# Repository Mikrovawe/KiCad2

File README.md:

# Input Output device

School assignment

In this assignment I received the schematic for this input/output device.
My task was to design the functional blocks and create the documentation as well as designing the 4-layer pcb using KiCad.

In file XX there is the planning of the design

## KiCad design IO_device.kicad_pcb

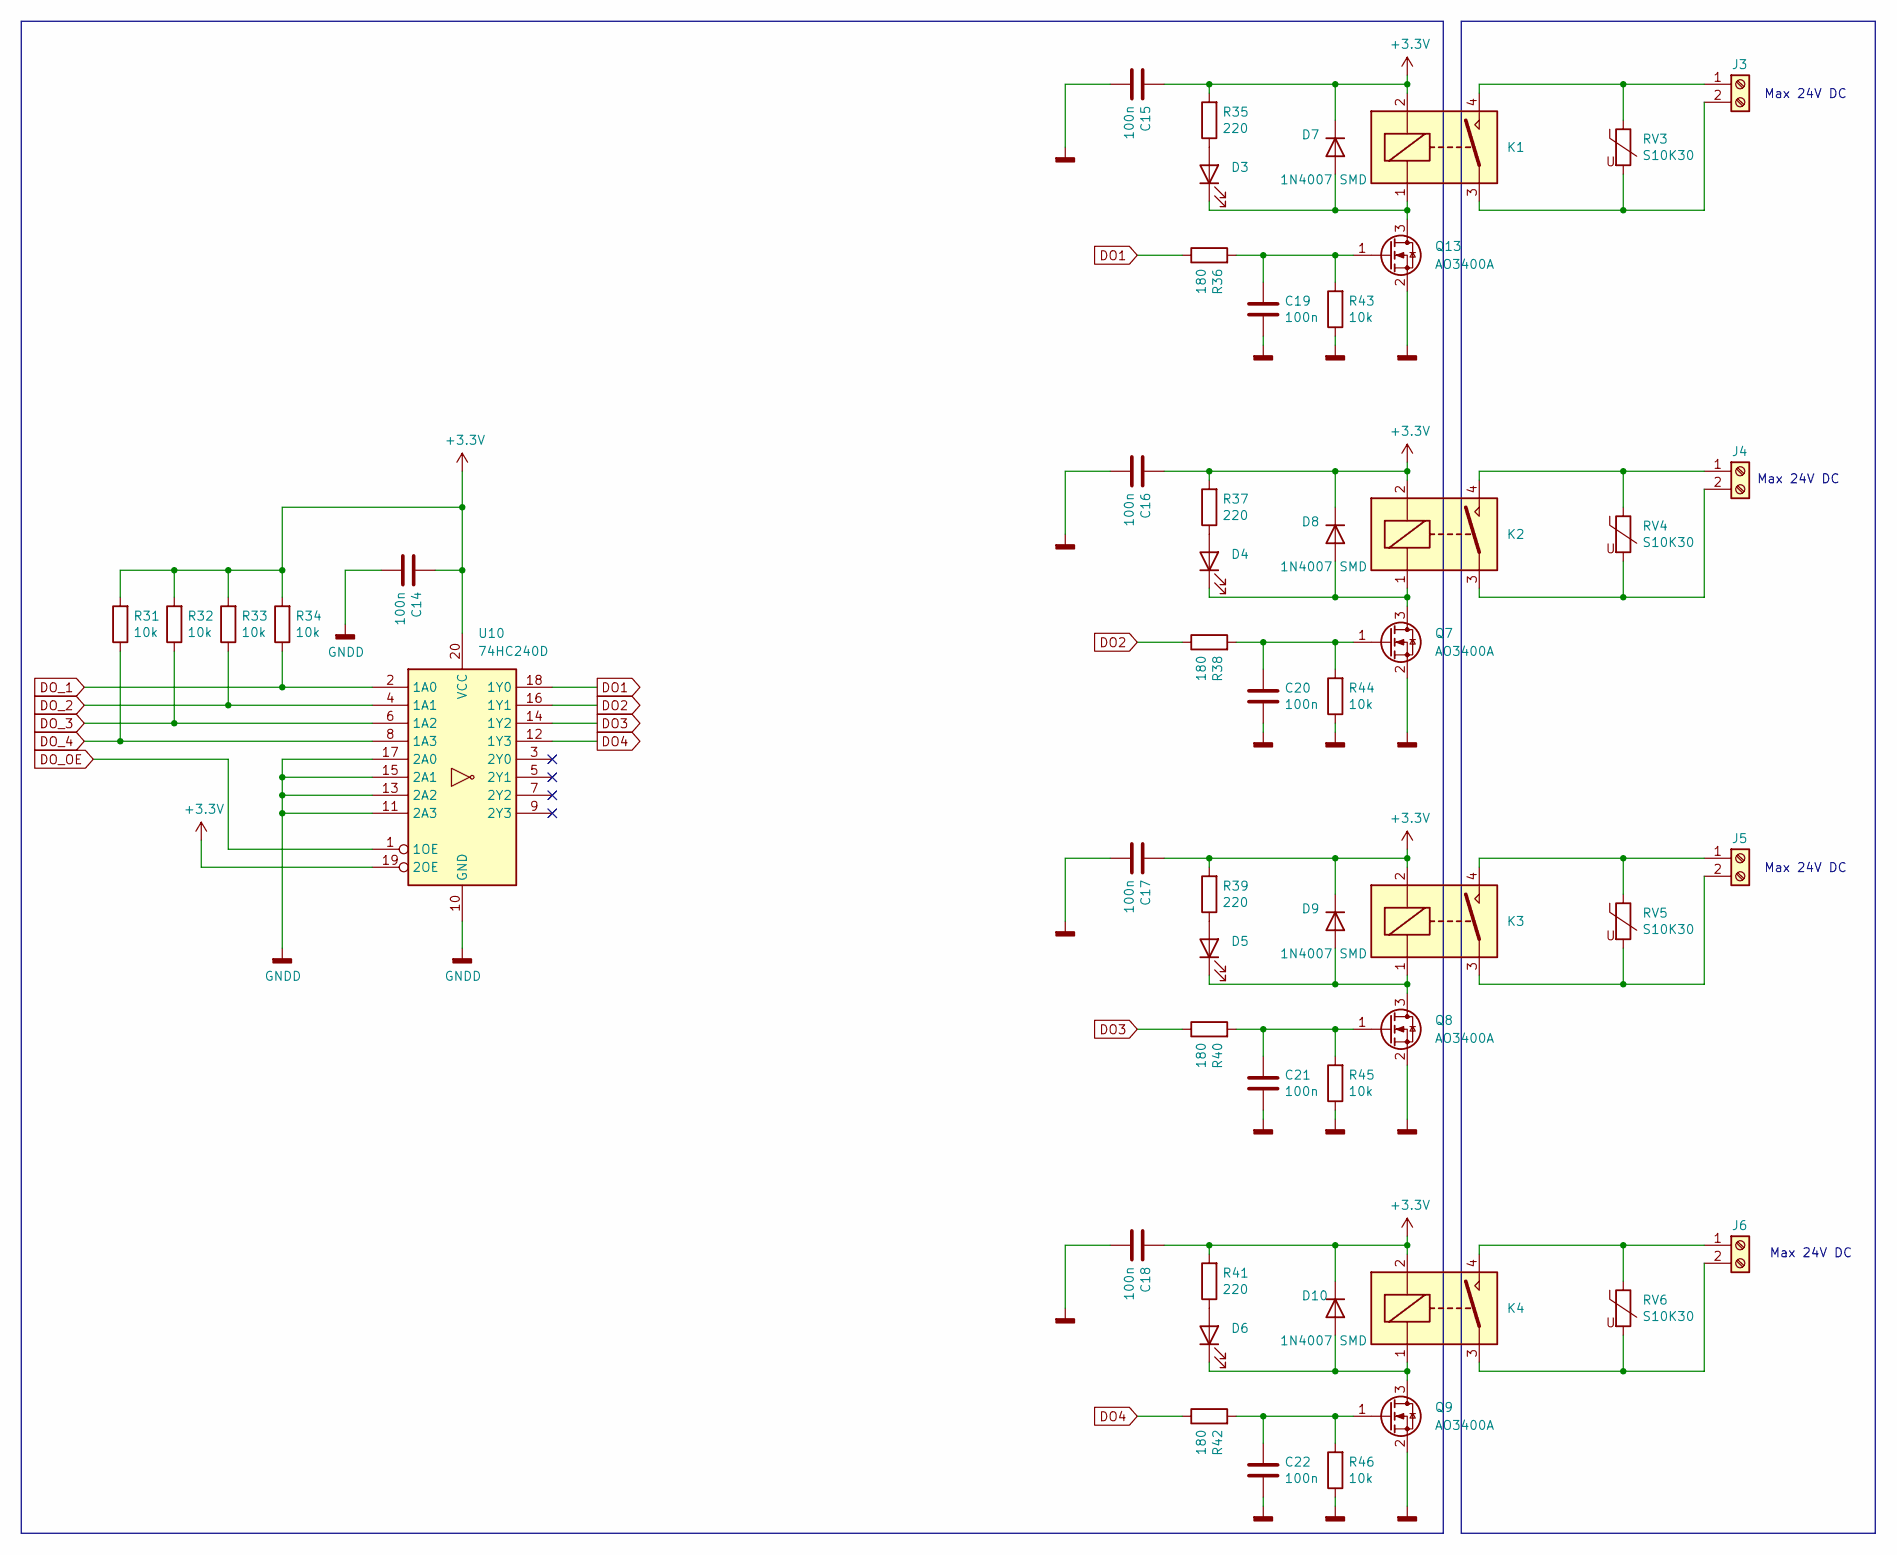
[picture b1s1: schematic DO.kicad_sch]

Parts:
C14, C15, C16, C17, C18, C19, C20, C21, C22: 100n; C_1206_3216Metric
D3, D4, D5, D6: Green LED 3mm; D_1206_3216Metric
D7, D8, D9, D10: 1N4007 SMD; D_SOD-123
J3, J4, J5, J6: Screw_Terminal_01x02; TerminalBlock_Phoenix_MKDS-3-2-5.08_1x02_P5.08mm_Horizontal
K1, K2, K3, K4: SDT-S-103DMR,000; 1461267-1
Q7, Q8, Q9, Q13: AO3400A; SOT-23
R31, R32, R33, R34, R43, R44, R45, R46: 10k; R_1206_3216Metric
R35, R37, R39, R41: 220; R_1206_3216Metric
R36, R38, R40, R42: 180; R_1206_3216Metric
RV3, RV4, RV5, RV6: S10K30; RV_Disc_D12mm_W5.1mm_P7.5mm
U10: 74HC240D; SOIC-20W_7.5x12.8mm_P1.27mm

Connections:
+3.3V: C14.1, C15.1, C16.1, C17.1, C18.1, D7.1 (K), D8.1 (K), D9.1 (K), D10.1 (K), K1.2, K2.2, K3.2, K4.2, R31.2, R32.2, R33.2, R34.2, R35.2, R37.2, R39.2, R41.2, U10.19 (2OE), U10.20 (VCC); also elsewhere on the board
DO1: R36.1, U10.18 (1Y0)
DO2: R38.1, U10.16 (1Y1)
DO3: R40.1, U10.14 (1Y2)
DO4: R42.1, U10.12 (1Y3)
DO_1: R34.1, U10.2 (1A0); also elsewhere on the board
DO_2: R33.1, U10.4 (1A1); also elsewhere on the board
DO_3: R32.1, U10.6 (1A2); also elsewhere on the board
DO_4: R31.1, U10.8 (1A3); also elsewhere on the board
DO_OE: U10.1 (1OE); also elsewhere on the board
GNDD: C14.2, C15.2, C16.2, C17.2, C18.2, C19.2, C20.2, C21.2, C22.2, Q7.2 (S), Q8.2 (S), Q9.2 (S), Q13.2 (S), R43.1, R44.1, R45.1, R46.1, U10.10 (GND), U10.11 (2A3), U10.13 (2A2), U10.15 (2A1), U10.17 (2A0); also elsewhere on the board
unnamed: D3.2 (A), R35.1
unnamed: D3.1 (K), D7.2 (A), K1.1, Q13.3 (D)
unnamed: D4.2 (A), R37.1
unnamed: D4.1 (K), D8.2 (A), K2.1, Q7.3 (D)
unnamed: D5.2 (A), R39.1
unnamed: D5.1 (K), D9.2 (A), K3.1, Q8.3 (D)
unnamed: D6.2 (A), R41.1
unnamed: D6.1 (K), D10.2 (A), K4.1, Q9.3 (D)
unnamed: J3.1, K1.4, RV3.1
unnamed: J3.2, K1.3, RV3.2
unnamed: J4.1, K2.4, RV4.1
unnamed: J4.2, K2.3, RV4.2
unnamed: J5.1, K3.4, RV5.1
unnamed: J5.2, K3.3, RV5.2
unnamed: J6.1, K4.4, RV6.1
unnamed: J6.2, K4.3, RV6.2
unnamed: C20.1, Q7.1 (G), R38.2, R44.2
unnamed: C21.1, Q8.1 (G), R40.2, R45.2
unnamed: C22.1, Q9.1 (G), R42.2, R46.2
unnamed: C19.1, Q13.1 (G), R36.2, R43.2

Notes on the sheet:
Max 24V DC

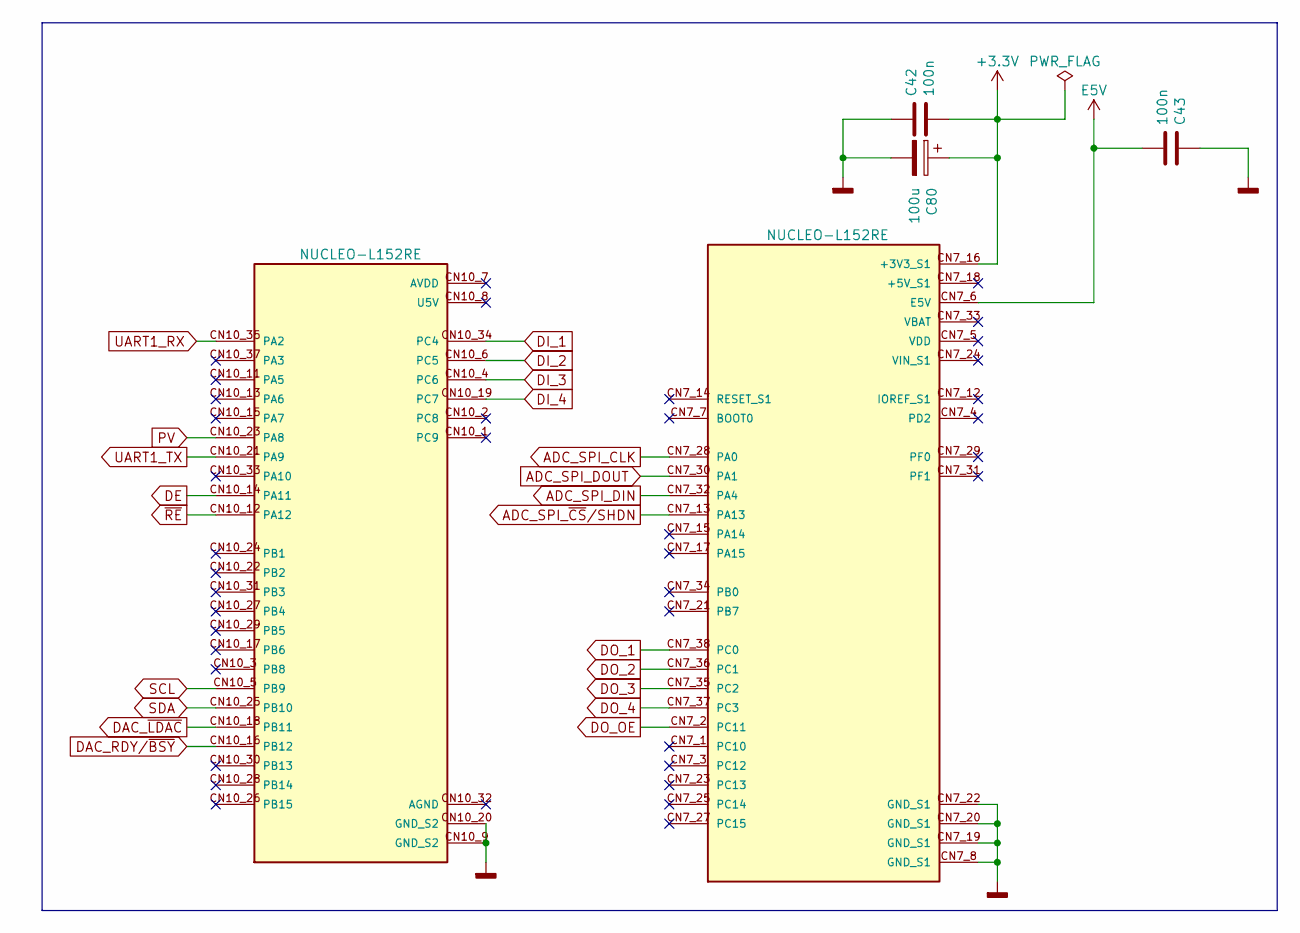
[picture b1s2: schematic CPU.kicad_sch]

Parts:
C42, C43: 100n; C_1206_3216Metric; Voltage 250V
C80: 100u; CP_Elec_6.3x7.7
U28: NUCLEO-L152RE; ST_NUCLEO-F303RE; PARTREV 14

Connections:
+3.3V: C42.2, C80.1, U28.CN7_16 (+3V3_S1); also elsewhere on the board
ADC_SPI_CLK: U28.CN7_28 (PA0); also elsewhere on the board
ADC_SPI_DIN: U28.CN7_32 (PA4); also elsewhere on the board
ADC_SPI_DOUT: U28.CN7_30 (PA1); also elsewhere on the board
ADC_SPI_~CS/SHDN: U28.CN7_13 (PA13); also elsewhere on the board
DAC_RDY/~BSY: U28.CN10_16 (PB12); also elsewhere on the board
DAC_~LDAC: U28.CN10_18 (PB11); also elsewhere on the board
DE: U28.CN10_14 (PA11); also elsewhere on the board
DI_1: U28.CN10_34 (PC4); also elsewhere on the board
DI_2: U28.CN10_6 (PC5); also elsewhere on the board
DI_3: U28.CN10_4 (PC6); also elsewhere on the board
DI_4: U28.CN10_19 (PC7); also elsewhere on the board
DO_1: U28.CN7_38 (PC0); also elsewhere on the board
DO_2: U28.CN7_36 (PC1); also elsewhere on the board
DO_3: U28.CN7_35 (PC2); also elsewhere on the board
DO_4: U28.CN7_37 (PC3); also elsewhere on the board
DO_OE: U28.CN7_2 (PC11); also elsewhere on the board
E5V: C43.2, U28.CN7_6 (E5V); also elsewhere on the board
GNDD: C42.1, C43.1, C80.2, U28.CN7_8 (GND_S1), U28.CN7_19 (GND_S1), U28.CN7_20 (GND_S1), U28.CN7_22 (GND_S1), U28.CN10_9 (GND_S2), U28.CN10_20 (GND_S2); also elsewhere on the board
PV: U28.CN10_23 (PA8); also elsewhere on the board
SCL: U28.CN10_5 (PB9); also elsewhere on the board
SDA: U28.CN10_25 (PB10); also elsewhere on the board
UART1_RX: U28.CN10_35 (PA2); also elsewhere on the board
UART1_TX: U28.CN10_21 (PA9); also elsewhere on the board
~RE: U28.CN10_12 (PA12); also elsewhere on the board

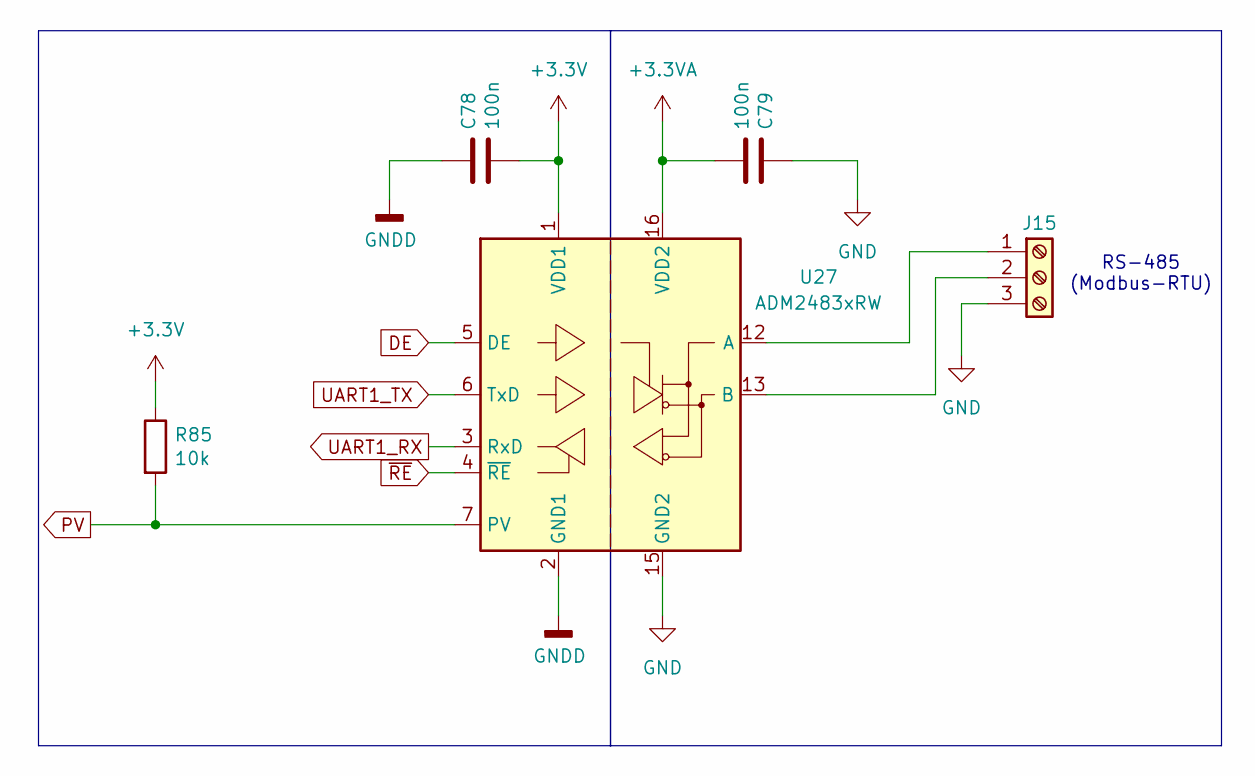
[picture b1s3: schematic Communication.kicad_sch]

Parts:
C78, C79: 100n; C_1206_3216Metric; Voltage 250V
J15: Screw_Terminal_01x03; TerminalBlock_Phoenix_MKDS-3-3-5.08_1x03_P5.08mm_Horizontal
R85: 10k; C_1206_3216Metric
U27: ADM2483xRW; SOIC-16W_7.5x10.3mm_P1.27mm

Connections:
+3.3V: C78.2, R85.1, U27.1 (VDD1); also elsewhere on the board
+3.3VA: C79.2, U27.16 (VDD2); also elsewhere on the board
DE: U27.5 (DE); also elsewhere on the board
GND: C79.1, J15.3, U27.9 (GND2), U27.15 (GND2); also elsewhere on the board
GNDD: C78.1, U27.2 (GND1), U27.8 (GND1); also elsewhere on the board
unnamed: J15.1, U27.12 (A)
unnamed: J15.2, U27.13 (B)
PV: R85.2, U27.7 (PV); also elsewhere on the board
UART1_RX: U27.3 (RxD); also elsewhere on the board
UART1_TX: U27.6 (TxD); also elsewhere on the board
~RE: U27.4 (~RE); also elsewhere on the board

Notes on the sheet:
RS-485 (Modbus-RTU)

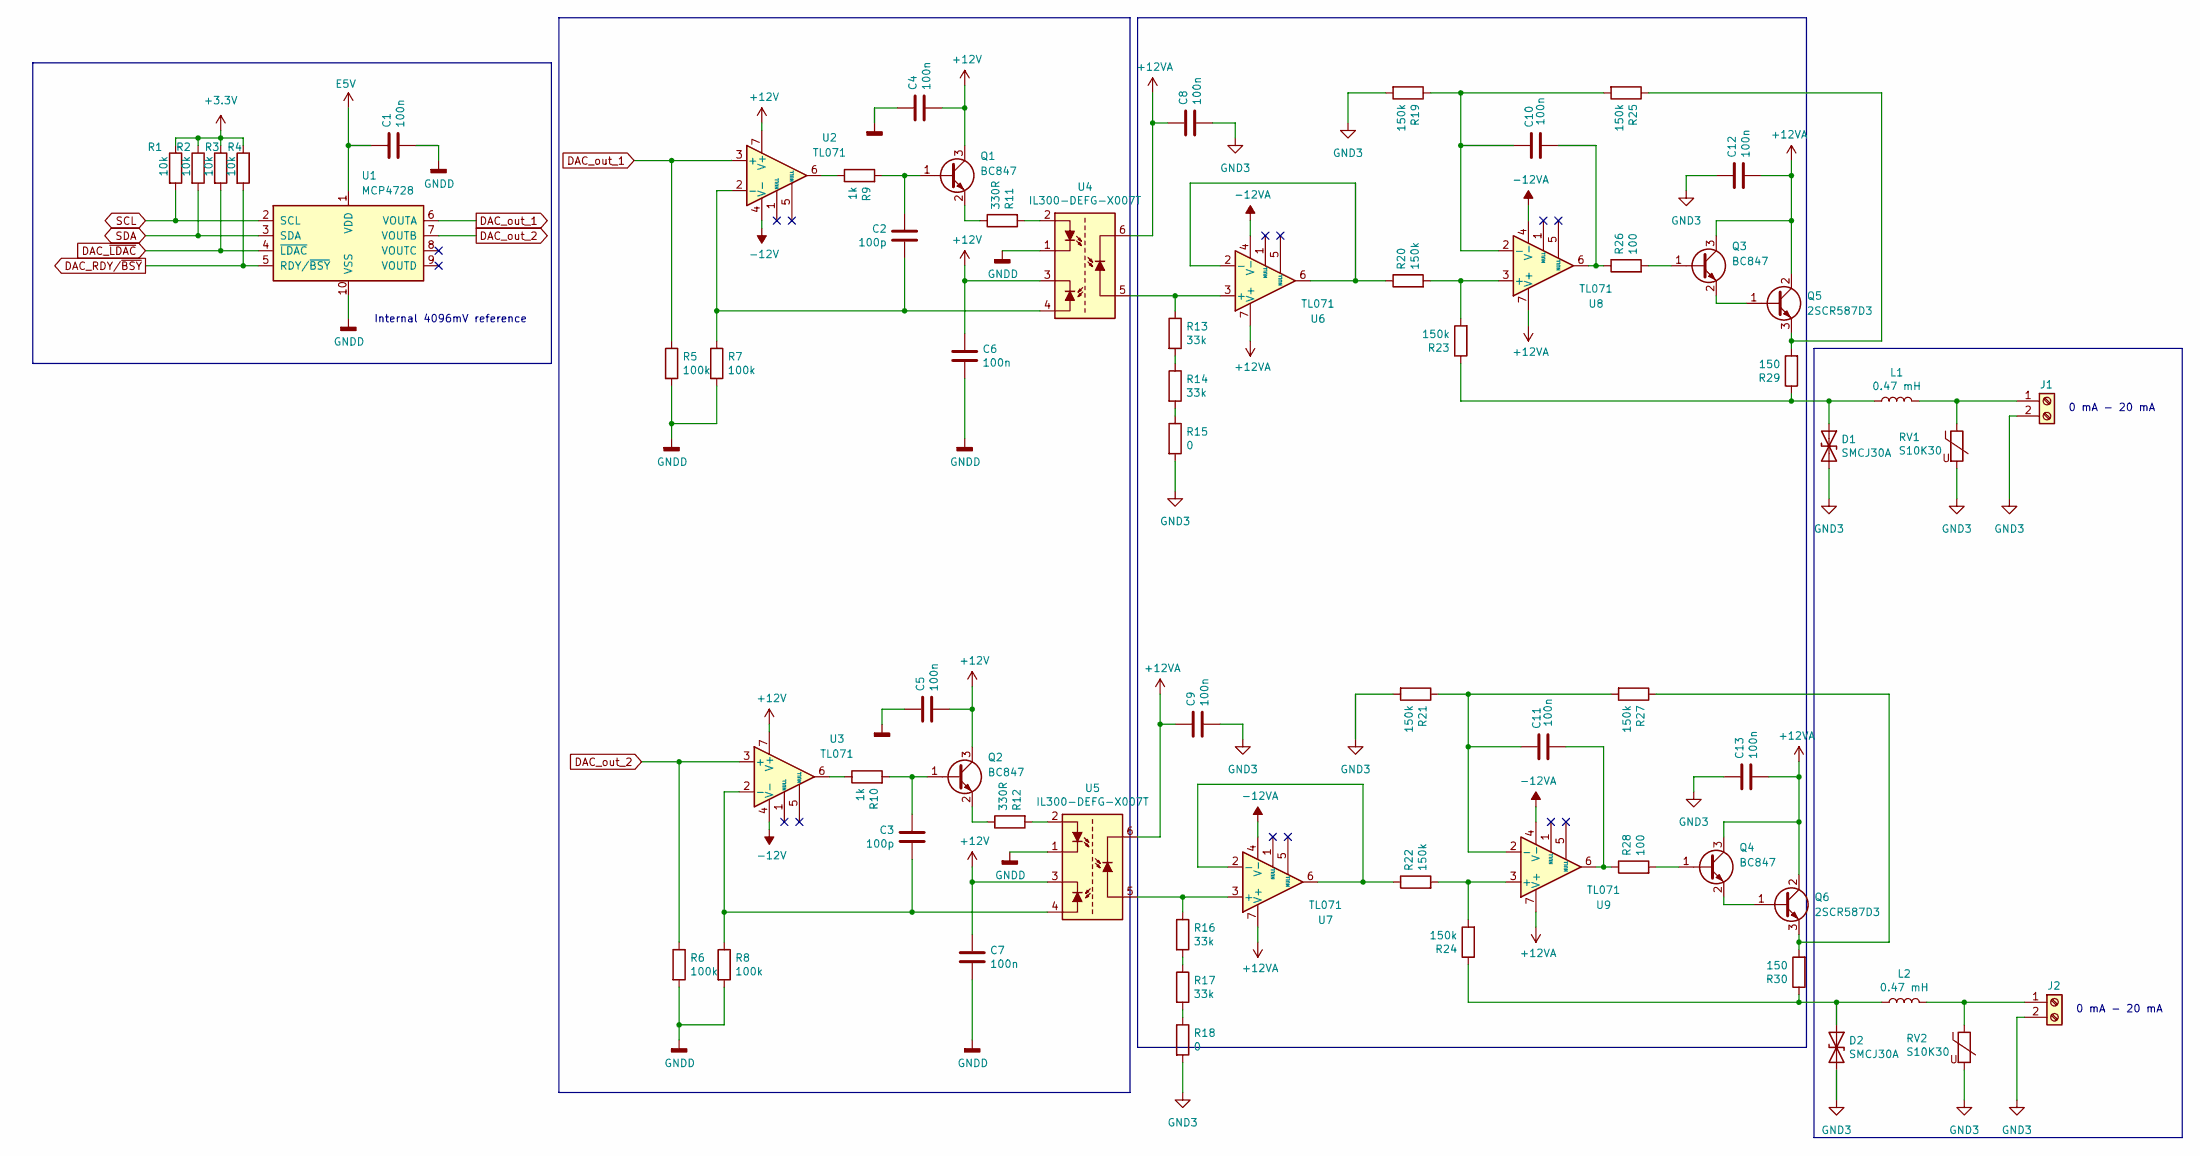
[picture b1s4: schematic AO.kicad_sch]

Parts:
C1, C4, C5, C8, C9, C12, C13: 100n; C_1206_3216Metric
C2, C3: 100p; C_1206_3216Metric
C6, C7, C10, C11: 100n; R_1206_3216Metric
D1, D2: SMCJ30A; D_SMC
J1, J2: Screw_Terminal_01x02; TerminalBlock_Phoenix_MKDS-3-2-5.08_1x02_P5.08mm_Horizontal
L1, L2: 0.47 mH; L_Radial_D7.8mm_P5.00mm_Fastron_07HCP
Q1, Q2, Q3, Q4: BC847; SOT-23
Q5, Q6: 2SCR587D3; TO-252-2
R1, R2, R3, R4: 10k; R_1206_3216Metric
R5, R6, R7, R8: 100k; R_1206_3216Metric
R9, R10: 1k; D_1206_3216Metric
R11, R12: 330R; R_1020_2550Metric
R13, R14, R16, R17: 33k; R_1206_3216Metric
R15, R18: 0; R_1206_3216Metric
R19, R20, R21, R22, R23, R24, R25, R27: 150k; C_1206_3216Metric
R26, R28: 100; C_1206_3216Metric
R29, R30: 150; C_1206_3216Metric
RV1, RV2: S10K30; RV_Disc_D12mm_W5.1mm_P7.5mm
U1: MCP4728; MSOP-10_3x3mm_P0.5mm
U2, U3, U6, U7, U8, U9: TL071; SOIC-8_3.9x4.9mm_P1.27mm
U4, U5: IL300-DEFG-X007T; DIP-8_W8.89mm_SMDSocket_LongPads

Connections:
+3.3V: R1.1, R2.1, R3.1, R4.1; also elsewhere on the board
+12V: C4.1, C5.1, C6.2, C7.2, Q1.3 (C), Q2.3 (C), U2.7 (V+), U3.7 (V+), U4.3, U5.3; also elsewhere on the board
+12VA: C8.2, C9.2, C12.1, C13.1, Q3.3 (C), Q4.3 (C), Q5.2 (C), Q6.2 (C), U4.6, U5.6, U6.7 (V+), U7.7 (V+), U8.7 (V+), U9.7 (V+); also elsewhere on the board
-12V: U2.4 (V-), U3.4 (V-); also elsewhere on the board
-12VA: U6.4 (V-), U7.4 (V-), U8.4 (V-), U9.4 (V-); also elsewhere on the board
DAC_RDY/~BSY: R4.2, U1.5 (RDY/~BSY); also elsewhere on the board
DAC_out_1: R5.1, U1.6 (VOUTA), U2.3 (+)
DAC_out_2: R6.1, U1.7 (VOUTB), U3.3 (+)
DAC_~LDAC: R3.2, U1.4 (~LDAC); also elsewhere on the board
E5V: C1.2, U1.1 (VDD); also elsewhere on the board
GND3: C8.1, C9.1, C12.2, C13.2, D1.2 (A2), D2.2 (A2), J1.2, J2.2, R15.2, R18.2, R19.2, R21.2, RV1.2, RV2.2; also elsewhere on the board
GNDD: C1.1, C4.2, C5.2, C6.1, C7.1, R5.2, R6.2, R7.2, R8.2, U1.10 (VSS), U4.1, U5.1; also elsewhere on the board
unnamed: C10.1, R26.1, U8.6
unnamed: C11.1, R28.1, U9.6
unnamed: D1.1 (A1), L1.2, R23.1, R29.1
unnamed: D2.1 (A1), L2.2, R24.1, R30.1
unnamed: J1.1, L1.1, RV1.1
unnamed: J2.1, L2.1, RV2.1
unnamed: C2.1, Q1.1 (B), R9.2
unnamed: Q1.2 (E), R11.1
unnamed: C3.1, Q2.1 (B), R10.2
unnamed: Q2.2 (E), R12.1
unnamed: Q3.1 (B), R26.2
unnamed: Q3.2 (E), Q5.1 (B)
unnamed: Q4.1 (B), R28.2
unnamed: Q4.2 (E), Q6.1 (B)
unnamed: Q5.3 (E), R25.1, R29.2
unnamed: Q6.3 (E), R27.1, R30.2
unnamed: R9.1, U2.6
unnamed: R10.1, U3.6
unnamed: R11.2, U4.2
unnamed: R12.2, U5.2
unnamed: R13.2, R14.1
unnamed: R14.2, R15.1
unnamed: R16.2, R17.1
unnamed: R17.2, R18.1
unnamed: C2.2, R7.1, U2.2 (-), U4.4
unnamed: C3.2, R8.1, U3.2 (-), U5.4
unnamed: R13.1, U4.5, U6.3 (+)
unnamed: R20.1, U6.2 (-), U6.6
unnamed: R16.1, U5.5, U7.3 (+)
unnamed: R22.1, U7.2 (-), U7.6
unnamed: R20.2, R23.2, U8.3 (+)
unnamed: C10.2, R19.1, R25.2, U8.2 (-)
unnamed: R22.2, R24.2, U9.3 (+)
unnamed: C11.2, R21.1, R27.2, U9.2 (-)
SCL: R1.2, U1.2 (SCL); also elsewhere on the board
SDA: R2.2, U1.3 (SDA); also elsewhere on the board

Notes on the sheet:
0 mA - 20 mA
Internal 4096mV reference

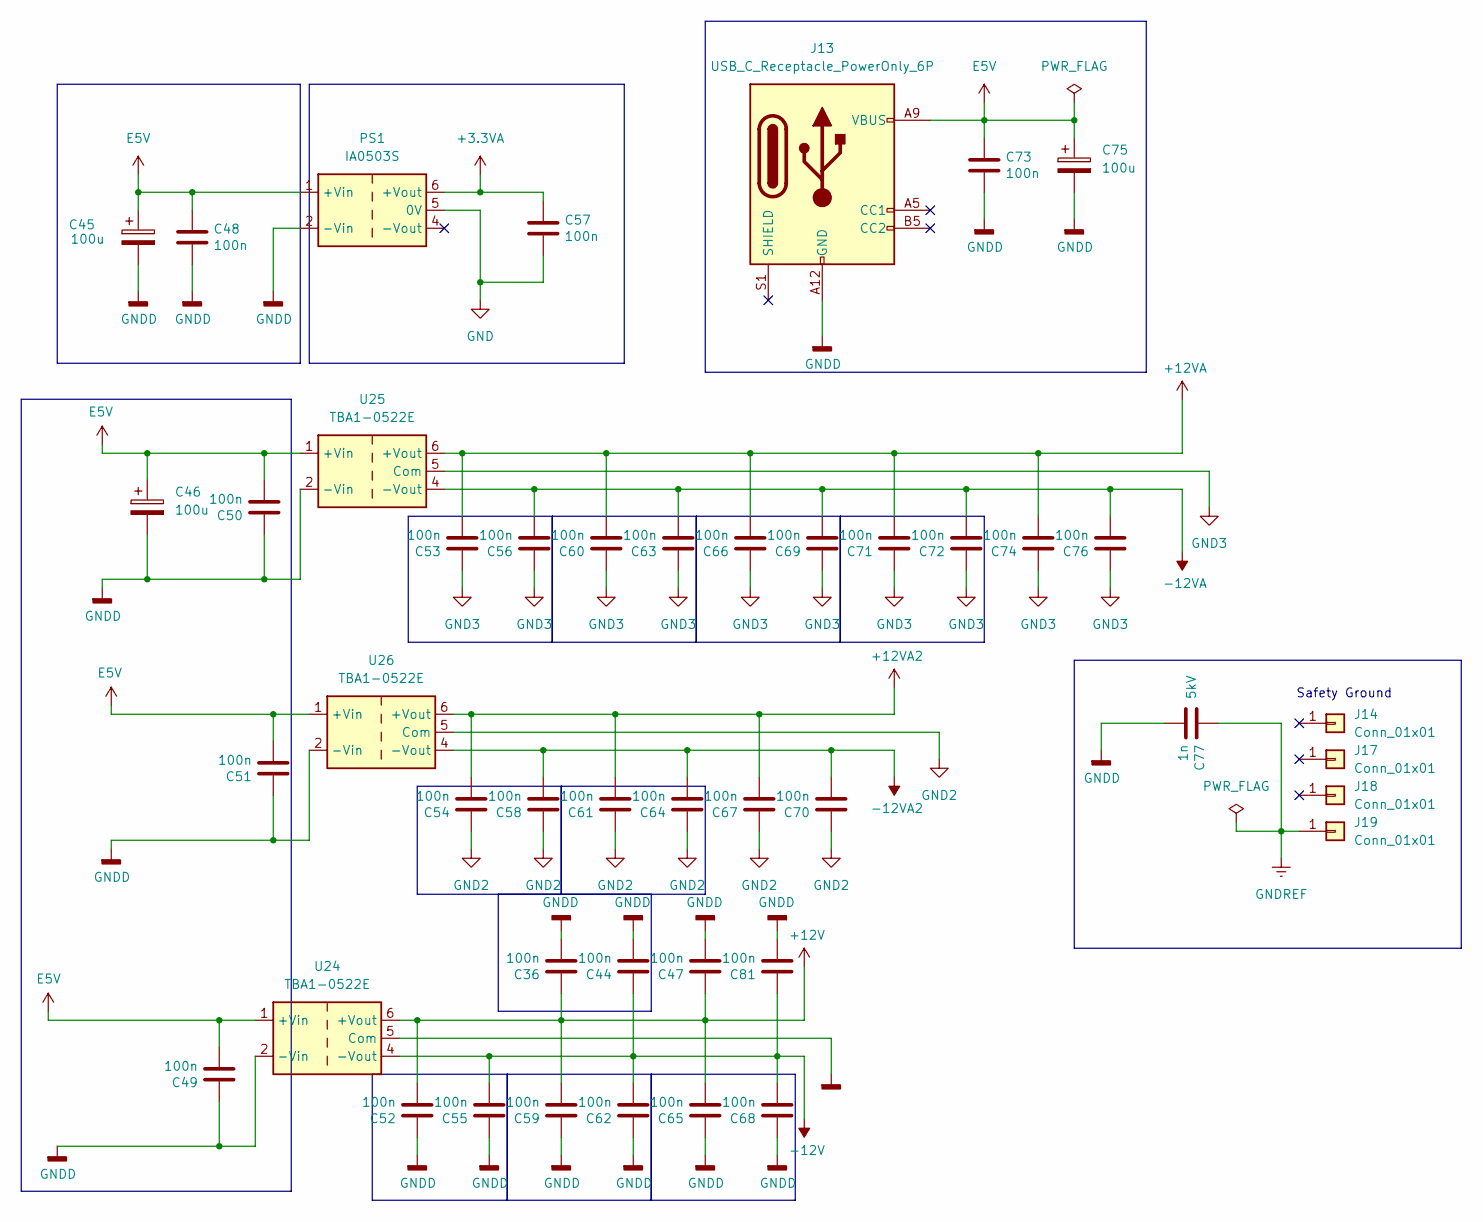
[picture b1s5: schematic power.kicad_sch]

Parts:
C36, C44, C47, C49, C50, C51, C52, C53, C54, C55, C56, C58, C59, C60, C61, C62, C63, C64, C65, C66, C67, C68, C69, C70, C71, C72, C74, C76, C81: 100n; C_1206_3216Metric
C45, C46, C75: 100u; CP_Elec_6.3x7.7
C48, C57, C73: 100n; C_1206_3216Metric; Voltage 250V
C77: 1n; C_2220_5750Metric; Voltage 5kV
J13: USB_C_Receptacle_PowerOnly_6P; CUI_UJC-HP-3-SMT-TR
J14, J17, J18, J19: Conn_01x01; MountingHole_3.5mm_Pad
PS1: IA0503S; Converter_DCDC_XP_POWER-IAxxxxS_THT
U24, U25, U26: TBA1-0522E; Converter_DCDC_TRACO_TBA1-xxxxE_Dual_THT

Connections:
+3.3VA: C57.1, PS1.6 (+Vout); also elsewhere on the board
+12V: C36.2, C47.2, C52.1, C59.1, C65.1, U24.6 (+Vout); also elsewhere on the board
+12VA: C53.1, C60.1, C66.1, C71.1, C74.1, U25.6 (+Vout); also elsewhere on the board
+12VA2: C54.1, C61.1, C67.1, U26.6 (+Vout); also elsewhere on the board
-12V: C44.2, C55.1, C62.1, C68.1, C81.2, U24.4 (-Vout); also elsewhere on the board
-12VA: C56.1, C63.1, C69.1, C72.1, C76.1, U25.4 (-Vout); also elsewhere on the board
-12VA2: C58.1, C64.1, C70.1, U26.4 (-Vout); also elsewhere on the board
E5V: C45.1, C46.1, C48.1, C49.1, C50.1, C51.1, C73.1, C75.1, J13.A9 (VBUS), J13.B9 (VBUS), PS1.1 (+Vin), U24.1 (+Vin), U25.1 (+Vin), U26.1 (+Vin); also elsewhere on the board
GND: C57.2, PS1.5 (0V); also elsewhere on the board
GND2: C54.2, C58.2, C61.2, C64.2, C67.2, C70.2, U26.5 (Com); also elsewhere on the board
GND3: C53.2, C56.2, C60.2, C63.2, C66.2, C69.2, C71.2, C72.2, C74.2, C76.2, U25.5 (Com); also elsewhere on the board
GNDD: C36.1, C44.1, C45.2, C46.2, C47.1, C48.2, C49.2, C50.2, C51.2, C52.2, C55.2, C59.2, C62.2, C65.2, C68.2, C73.2, C75.2, C77.2, C81.1, J13.A12 (GND), J13.B12 (GND), PS1.2 (-Vin), U24.2 (-Vin), U24.5 (Com), U25.2 (-Vin), U26.2 (-Vin); also elsewhere on the board
GNDREF: C77.1, J19.1

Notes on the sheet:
Safety Ground

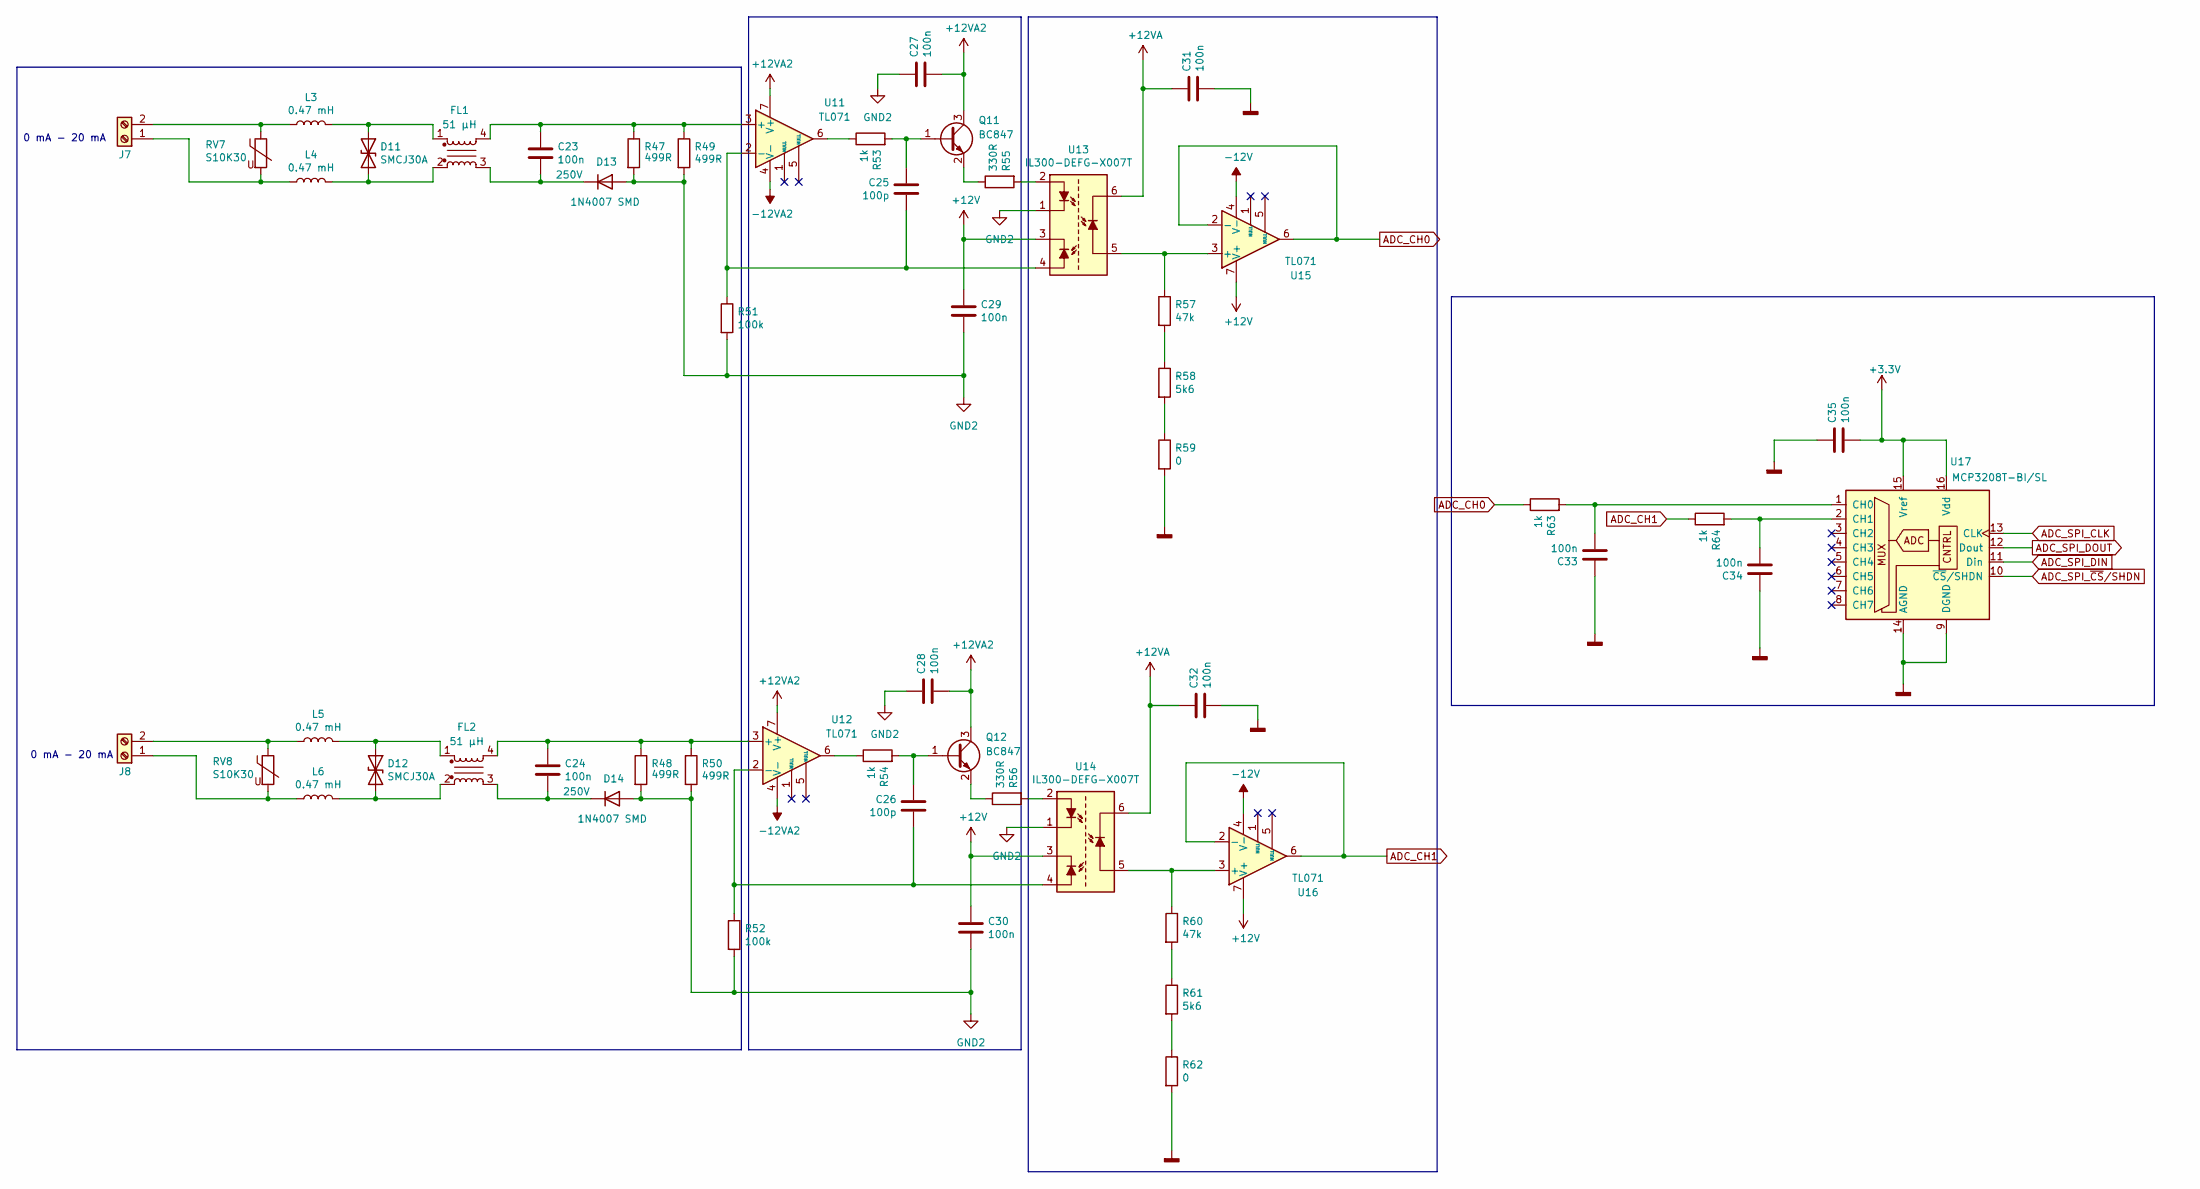
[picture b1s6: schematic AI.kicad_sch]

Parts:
C23, C24: 100n; C_1206_3216Metric; Voltage 250V
C25, C26: 100p; C_1206_3216Metric
C27, C28, C31, C32, C33, C34, C35: 100n; C_1206_3216Metric
C29, C30: 100n; R_1206_3216Metric
D11, D12: SMCJ30A; D_SMC
D13, D14: 1N4007 SMD; D_SOD-123
FL1, FL2: 51 µH; L_CommonMode_Wuerth_WE-SL2
J7, J8: Screw_Terminal_01x02; TerminalBlock_Phoenix_MKDS-3-2-5.08_1x02_P5.08mm_Horizontal
L3, L4, L5, L6: 0.47 mH; L_Radial_D7.8mm_P5.00mm_Fastron_07HCP
Q11, Q12: BC847; SOT-23
R47, R48, R49, R50: 499R; R_1206_3216Metric
R51, R52: 100k; R_1206_3216Metric
R53, R54, R63, R64: 1k; D_1206_3216Metric
R55, R56: 330R; R_1020_2550Metric
R57, R60: 47k; C_1206_3216Metric
R58, R61: 5k6; R_1206_3216Metric
R59, R62: 0; R_1206_3216Metric
RV7, RV8: S10K30; RV_Disc_D12mm_W5.1mm_P7.5mm
U11, U12, U15, U16: TL071; SOIC-8_3.9x4.9mm_P1.27mm
U13, U14: IL300-DEFG-X007T; DIP-8_W8.89mm_SMDSocket_LongPads
U17: MCP3208T-BI/SL; SOIC-16W_5.3x10.2mm_P1.27mm

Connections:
+3.3V: C35.1, U17.15 (Vref), U17.16 (Vdd); also elsewhere on the board
+12V: C29.2, C30.2, U13.3, U14.3, U15.7 (V+), U16.7 (V+); also elsewhere on the board
+12VA: C31.2, C32.2, U13.6, U14.6; also elsewhere on the board
+12VA2: C27.1, C28.1, Q11.3 (C), Q12.3 (C), U11.7 (V+), U12.7 (V+); also elsewhere on the board
-12V: U15.4 (V-), U16.4 (V-); also elsewhere on the board
-12VA2: U11.4 (V-), U12.4 (V-); also elsewhere on the board
ADC_CH0: R63.1, U15.2 (-), U15.6
ADC_CH1: R64.1, U16.2 (-), U16.6
ADC_SPI_CLK: U17.13 (CLK); also elsewhere on the board
ADC_SPI_DIN: U17.11 (Din); also elsewhere on the board
ADC_SPI_DOUT: U17.12 (Dout); also elsewhere on the board
ADC_SPI_~CS/SHDN: U17.10 (~CS/SHDN); also elsewhere on the board
GND2: C27.2, C28.2, C29.1, C30.1, D13.2 (A), D14.2 (A), R47.2, R48.2, R49.2, R50.2, R51.2, R52.2, U13.1, U14.1; also elsewhere on the board
GNDD: C31.1, C32.1, C33.2, C34.2, C35.2, R59.2, R62.2, U17.9 (DGND), U17.14 (AGND); also elsewhere on the board
unnamed: D11.1 (A1), FL1.1, L3.1
unnamed: D11.2 (A2), FL1.2, L4.1
unnamed: D12.1 (A1), FL2.1, L5.1
unnamed: D12.2 (A2), FL2.2, L6.1
unnamed: C23.2, D13.1 (K), FL1.3
unnamed: C24.2, D14.1 (K), FL2.3
unnamed: J7.1, L4.2, RV7.2
unnamed: J7.2, L3.2, RV7.1
unnamed: J8.1, L6.2, RV8.2
unnamed: J8.2, L5.2, RV8.1
unnamed: C25.1, Q11.1 (B), R53.2
unnamed: Q11.2 (E), R55.1
unnamed: C26.1, Q12.1 (B), R54.2
unnamed: Q12.2 (E), R56.1
unnamed: R53.1, U11.6
unnamed: R54.1, U12.6
unnamed: R55.2, U13.2
unnamed: R56.2, U14.2
unnamed: R57.2, R58.1
unnamed: R58.2, R59.1
unnamed: R60.2, R61.1
unnamed: R61.2, R62.1
unnamed: C23.1, FL1.4, R47.1, R49.1, U11.3 (+)
unnamed: C25.2, R51.1, U11.2 (-), U13.4
unnamed: C24.1, FL2.4, R48.1, R50.1, U12.3 (+)
unnamed: C26.2, R52.1, U12.2 (-), U14.4
unnamed: R57.1, U13.5, U15.3 (+)
unnamed: R60.1, U14.5, U16.3 (+)
unnamed: C33.1, R63.2, U17.1 (CH0)
unnamed: C34.1, R64.2, U17.2 (CH1)

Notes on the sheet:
0 mA - 20 mA
